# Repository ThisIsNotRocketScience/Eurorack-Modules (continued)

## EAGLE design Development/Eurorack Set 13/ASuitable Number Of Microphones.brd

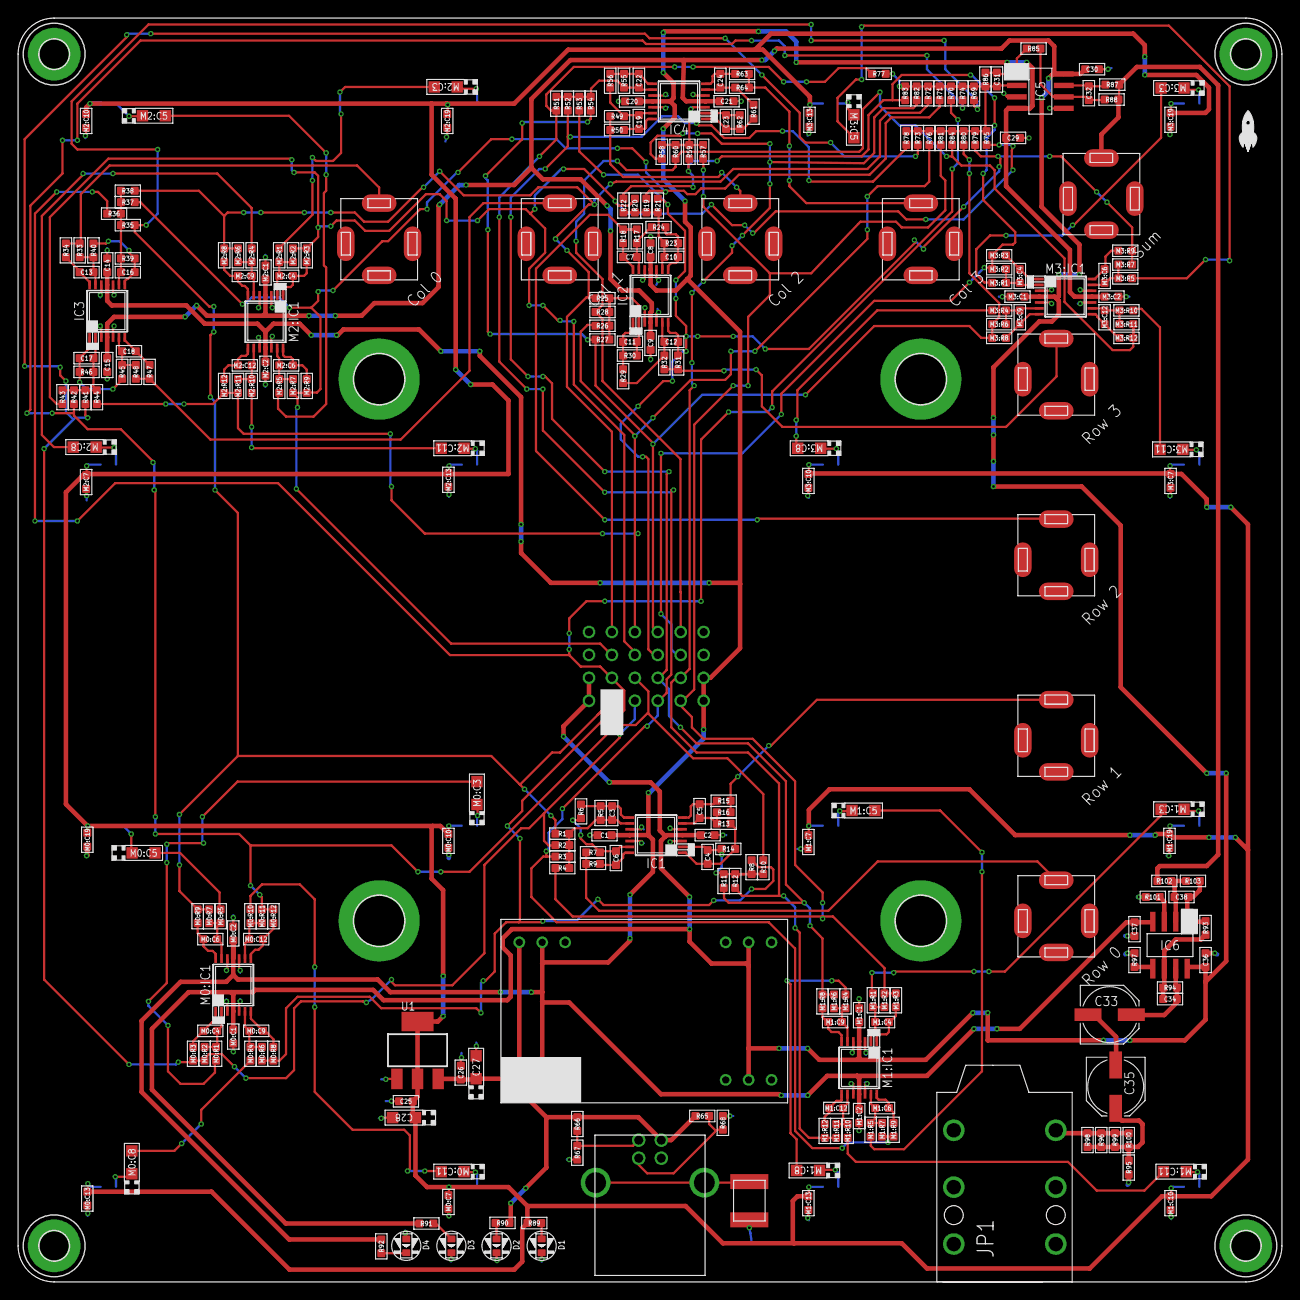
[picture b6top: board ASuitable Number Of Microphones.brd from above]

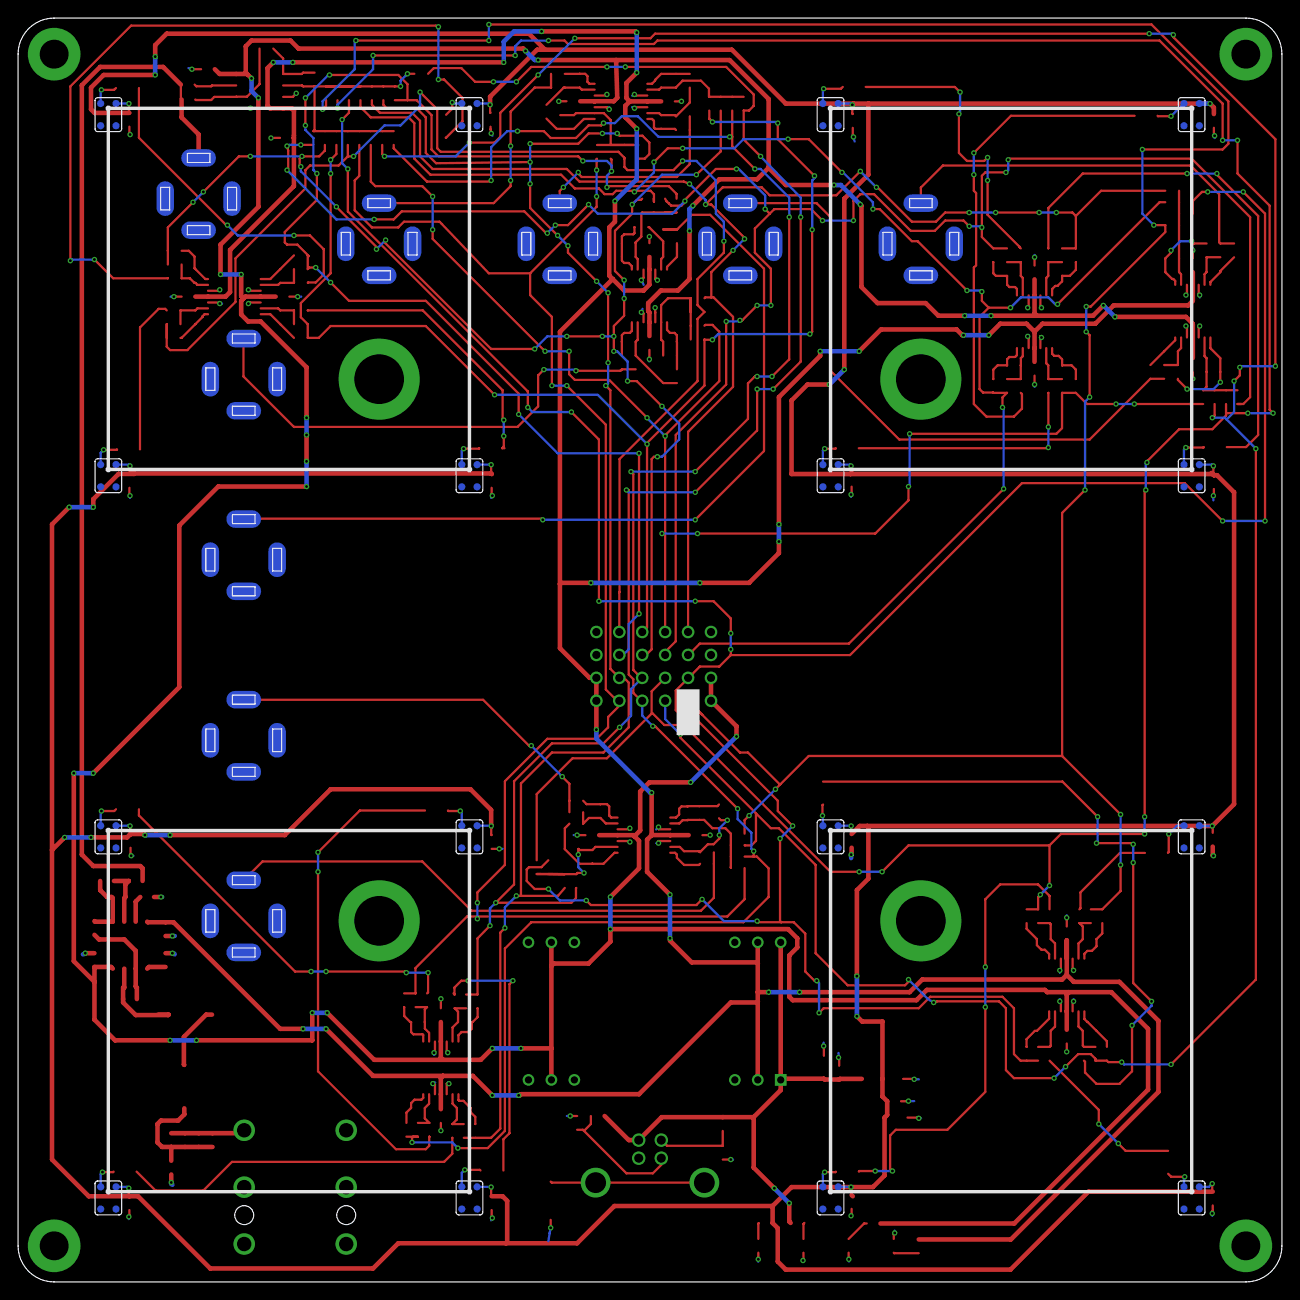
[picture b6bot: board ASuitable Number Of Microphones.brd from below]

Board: 2 copper layers, 140.0 x 140.0 mm, 299 parts (16 on the bottom side), 146 nets.

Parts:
C1, C2, C8, C9, C14, C15, C20, C21, C25, C26, C29, C30, C36, C37: 100n; C0603
C3, C4, C5, C6, C7, C10, C11, C12, C13, C16, C17, C18, C19, C22, C23, C24, C31, C32: 3.3n; C0603
C27, C28: 10u; CASE-A_3216
C33, C35: 100u; PANASONIC_D
C34, C38: 22p; C0603
D1, D2, D3, D4: LED0603
H1, H2, H3, H4: MOUNT-PAD-ROUND5.5; 5,5-PAD
H5, H6, H7, H8: MOUNT-PAD-ROUND3.2; 3,2-PAD
IC1, IC2, IC3, IC4: TL074TSSOP14; TSSOP14
IC5: TL072; SO08
IC6: NE5532D; SO08
J1, J2, J3, J4, J5, J6, J7, J8, J19: JACK; 3.5MM-JACK-SWITCH-13MM-NOHOLES
JP1: AUDIO-JACK-.25-INCH-HORIZ-PTH
L1: FERRITE_1812
M0:C1, M0:C2, M0:C7, M0:C10, M0:C13, M0:C19, M1:C1, M1:C2, M1:C7, M1:C10, M1:C13, M1:C19, M2:C1, M2:C2, M2:C7, M2:C10, M2:C13, M2:C19, M3:C1, M3:C2, M3:C7, M3:C10, M3:C13, M3:C19: 100n; C0603
M0:C3, M0:C5, M0:C8, M0:C11, M1:C3, M1:C5, M1:C8, M1:C11, M2:C3, M2:C5, M2:C8, M2:C11, M3:C3, M3:C5, M3:C8, M3:C11: 1u; CASE-A_3216
M0:C4, M0:C6, M0:C9, M0:C12, M1:C4, M1:C6, M1:C9, M1:C12, M2:C4, M2:C6, M2:C9, M2:C12, M3:C4, M3:C6, M3:C9, M3:C12: 3.3n; C0603
M0:IC1, M1:IC1, M2:IC1, M3:IC1: TL074TSSOP14; TSSOP14
M0:MIC0, M0:MIC1, M0:MIC2, M0:MIC3, M1:MIC0, M1:MIC1, M1:MIC2, M1:MIC3, M2:MIC0, M2:MIC1, M2:MIC2, M2:MIC3, M3:MIC0, M3:MIC1, M3:MIC2, M3:MIC3: SPU0410HR5H-PB
M0:R1, M0:R3, M0:R4, M0:R5, M0:R8, M0:R9, M0:R10, M0:R12, M1:R1, M1:R3, M1:R4, M1:R5, M1:R8, M1:R9, M1:R10, M1:R12, M2:R1, M2:R3, M2:R4, M2:R5, M2:R8, M2:R9, M2:R10, M2:R12, M3:R1, M3:R3, M3:R4, M3:R5, M3:R8, M3:R9, M3:R10, M3:R12: 100; R0603
M0:R2, M0:R6, M0:R7, M0:R11, M1:R2, M1:R6, M1:R7, M1:R11, M2:R2, M2:R6, M2:R7, M2:R11, M3:R2, M3:R6, M3:R7, M3:R11: 100k; R0603
R1, R2, R3, R4, R5, R6, R7, R8, R10, R11, R12, R13, R14, R16, R17, R19, R20, R21, R22, R23, R24, R25, R26, R27, R28, R29, R30, R32, R33, R35, R36, R37, R38, R39, R40, R41, R42, R43, R44, R45, R46, R48, R49, R51, R52, R53, R54, R55, R56, R57, R58, R59, R60, R61, R62, R64, R69, R70, R71, R72, R73, R74, R75, R76, R77, R78, R79, R80, R81, R82, R83, R84, R85, R86, R88: 100k; R0603
R9, R15, R18, R31, R34, R47, R50, R63, R87: 100; R0603
R65, R66: 75k; R0603
R67, R68: 49.9k; R0603
R89: 68; R0603
R90: 150; R0603
R91, R92: 560; R0603
R93, R94, R102, R103: 4.7k; R0603
R95: 56k; R0603
R96, R98, R99, R100: 220; R0603
R97, R101: 27; R0603
U1: CJ1117-3.3-1310190P1; SOT223
U$29: TOOMANYMICROPHONES
U$42: CINCONBRICK_12V; CINCONBRICK
U$51: TINRS_ARTWORKTINYDATE; JUSTATINYROCKET_DATECODE
X1: USB-B-FEMALE; FCI61729

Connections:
3.3V: C25.1, C28.+, M0:C7.2, M0:C10.2, M0:C13.2, M0:C19.2, M0:MIC0.P$1, M0:MIC1.P$1, M0:MIC2.P$1, M0:MIC3.P$1, M1:C7.2, M1:C10.2, M1:C13.2, M1:C19.2, M1:MIC0.P$1, M1:MIC1.P$1, M1:MIC2.P$1, M1:MIC3.P$1, M2:C7.2, M2:C10.2, M2:C13.2, M2:C19.2, M2:MIC0.P$1, M2:MIC1.P$1, M2:MIC2.P$1, M2:MIC3.P$1, M3:C7.2, M3:C10.2, M3:C13.2, M3:C19.2, M3:MIC0.P$1, M3:MIC1.P$1, M3:MIC2.P$1, M3:MIC3.P$1, R89.2, U1.2, U1.TER
5V: C26.1, C27.+, R65.2, R66.2, R90.2, U1.3, U$42.1, U$42.24, X1.1
12V: C2.1, C9.1, C15.1, C21.1, C30.1, C36.2, IC1.4, IC2.4, IC3.4, IC4.4, IC5.8, IC6.8, M0:C1.2, M0:IC1.4, M1:C1.2, M1:IC1.4, M2:C1.2, M2:IC1.4, M3:C1.2, M3:IC1.4, R91.2, U$29.+12@1, U$29.+12@2, U$42.11, U$42.14
-12V: C1.2, C8.2, C14.2, C20.2, C29.2, C37.1, IC1.11, IC2.11, IC3.11, IC4.11, IC5.4, IC6.4, M0:C2.1, M0:IC1.11, M1:C2.1, M1:IC1.11, M2:C2.1, M2:IC1.11, M3:C2.1, M3:IC1.11, R92.1, U$29.-12@1, U$29.-12@2, U$42.2, U$42.23
COL0_SUM: J4.TIP_B@1, J4.TIP_T@3, R33.2, R34.2
COL1_SUM: J5.TIP_B@1, J5.TIP_T@3, R47.2, R48.2
COL2_SUM: J6.TIP_B@1, J6.TIP_T@3, R49.2, R50.2
COL3_SUM: J7.TIP_B@1, J7.TIP_T@3, R63.2, R64.2
GND: C1.1, C2.2, C8.1, C9.2, C14.1, C15.2, C20.1, C21.2, C25.2, C26.2, C27.-, C28.-, C29.1, C30.2, C36.1, C37.2, D1.-, D2.-, D3.-, D4.+, H1.B5,5, H2.B5,5, H3.B5,5, H4.B5,5, IC1.3, IC1.5, IC1.10, IC1.12, IC2.3, IC2.5, IC2.10, IC2.12, IC3.3, IC3.5, IC3.10, IC3.12, IC4.3, IC4.5, IC4.10, IC4.12, IC5.3, IC5.5, J1.RING_B@1, J1.RING_T@3, J2.RING_B@1, J2.RING_T@3, J3.RING_B@1, J3.RING_T@3, J4.RING_B@1, J4.RING_T@3, J5.RING_B@1, J5.RING_T@3, J6.RING_B@1, J6.RING_T@3, J7.RING_B@1, J7.RING_T@3, J8.RING_B@1, J8.RING_T@3, J19.RING_B@1, J19.RING_T@3, JP1.P$2, JP1.P$3, JP1.P$4, L1.P$1, M0:C1.1, M0:C2.2, M0:C7.1, M0:C10.1, M0:C13.1, M0:C19.1, M0:IC1.3, M0:IC1.5, M0:IC1.10, M0:IC1.12, M0:MIC0.P$2, M0:MIC0.P$3, M0:MIC1.P$2, M0:MIC1.P$3, M0:MIC2.P$2, M0:MIC2.P$3, M0:MIC3.P$2, M0:MIC3.P$3, M1:C1.1, M1:C2.2, M1:C7.1, M1:C10.1, M1:C13.1, M1:C19.1, M1:IC1.3, M1:IC1.5, M1:IC1.10, M1:IC1.12, M1:MIC0.P$2, M1:MIC0.P$3, M1:MIC1.P$2, M1:MIC1.P$3, M1:MIC2.P$2, M1:MIC2.P$3, M1:MIC3.P$2, M1:MIC3.P$3, M2:C1.1, M2:C2.2, M2:C7.1, M2:C10.1, M2:C13.1, M2:C19.1, M2:IC1.3, M2:IC1.5, M2:IC1.10, M2:IC1.12, M2:MIC0.P$2, M2:MIC0.P$3, M2:MIC1.P$2, M2:MIC1.P$3, M2:MIC2.P$2, M2:MIC2.P$3, M2:MIC3.P$2, M2:MIC3.P$3, M3:C1.1, M3:C2.2, M3:C7.1, M3:C10.1, M3:C13.1, M3:C19.1, M3:IC1.3, M3:IC1.5, M3:IC1.10, M3:IC1.12, M3:MIC0.P$2, M3:MIC0.P$3, M3:MIC1.P$2, M3:MIC1.P$3, M3:MIC2.P$2, M3:MIC2.P$3, M3:MIC3.P$2, M3:MIC3.P$3, R67.1, R68.1, R95.2, R97.2, R101.2, U1.1, U$29.GND@1, U$29.GND@2, U$29.GND@3, U$29.GND@4, U$42.3, U$42.10, U$42.12, U$42.13, U$42.15, U$42.22, X1.4
M0:N$1: M0:C6.2, M0:IC1.13, M0:R5.2, M0:R7.1
M0:N$2: M0:C6.1, M0:IC1.14, M0:R9.1
M0:N$3: M0:C4.2, M0:IC1.2, M0:R1.2, M0:R2.1
M0:N$4: M0:C4.1, M0:IC1.1, M0:R3.1
M0:N$5: M0:C9.2, M0:IC1.6, M0:R4.2, M0:R6.1
M0:N$7: M0:C12.2, M0:IC1.9, M0:R10.2, M0:R11.1
M0:N$9: M0:C9.1, M0:IC1.7, M0:R8.1
M0:N$10: M0:C12.1, M0:IC1.8, M0:R12.1
M0:N$14: M0:C11.-, M0:R10.1
M0:N$15: M0:C11.+, M0:MIC3.P$4
M0:N$16: M0:C8.+, M0:MIC2.P$4
M0:N$17: M0:C5.-, M0:R5.1
M0:N$18: M0:C5.+, M0:MIC0.P$4
M0:N$19: M0:C8.-, M0:R4.1
M0:N$20: M0:C3.+, M0:MIC1.P$4
M0:N$21: M0:C3.-, M0:R1.1
M1:N$1: M1:C6.2, M1:IC1.13, M1:R5.2, M1:R7.1
M1:N$2: M1:C6.1, M1:IC1.14, M1:R9.1
M1:N$3: M1:C4.2, M1:IC1.2, M1:R1.2, M1:R2.1
M1:N$4: M1:C4.1, M1:IC1.1, M1:R3.1
M1:N$5: M1:C9.2, M1:IC1.6, M1:R4.2, M1:R6.1
M1:N$7: M1:C12.2, M1:IC1.9, M1:R10.2, M1:R11.1
M1:N$9: M1:C9.1, M1:IC1.7, M1:R8.1
M1:N$10: M1:C12.1, M1:IC1.8, M1:R12.1
M1:N$14: M1:C11.-, M1:R10.1
M1:N$15: M1:C11.+, M1:MIC3.P$4
M1:N$16: M1:C8.+, M1:MIC2.P$4
M1:N$17: M1:C5.-, M1:R5.1
M1:N$18: M1:C5.+, M1:MIC0.P$4
M1:N$19: M1:C8.-, M1:R4.1
M1:N$20: M1:C3.+, M1:MIC1.P$4
M1:N$21: M1:C3.-, M1:R1.1
M2:N$1: M2:C6.2, M2:IC1.13, M2:R5.2, M2:R7.1
M2:N$2: M2:C6.1, M2:IC1.14, M2:R9.1
M2:N$3: M2:C4.2, M2:IC1.2, M2:R1.2, M2:R2.1
M2:N$4: M2:C4.1, M2:IC1.1, M2:R3.1
M2:N$5: M2:C9.2, M2:IC1.6, M2:R4.2, M2:R6.1
M2:N$7: M2:C12.2, M2:IC1.9, M2:R10.2, M2:R11.1
M2:N$9: M2:C9.1, M2:IC1.7, M2:R8.1
M2:N$10: M2:C12.1, M2:IC1.8, M2:R12.1
M2:N$14: M2:C11.-, M2:R10.1
M2:N$15: M2:C11.+, M2:MIC3.P$4
M2:N$16: M2:C8.+, M2:MIC2.P$4
M2:N$17: M2:C5.-, M2:R5.1
M2:N$18: M2:C5.+, M2:MIC0.P$4
M2:N$19: M2:C8.-, M2:R4.1
M2:N$20: M2:C3.+, M2:MIC1.P$4
M2:N$21: M2:C3.-, M2:R1.1
M3:N$1: M3:C6.2, M3:IC1.13, M3:R5.2, M3:R7.1
M3:N$2: M3:C6.1, M3:IC1.14, M3:R9.1
M3:N$3: M3:C4.2, M3:IC1.2, M3:R1.2, M3:R2.1
M3:N$4: M3:C4.1, M3:IC1.1, M3:R3.1
M3:N$5: M3:C9.2, M3:IC1.6, M3:R4.2, M3:R6.1
M3:N$7: M3:C12.2, M3:IC1.9, M3:R10.2, M3:R11.1
M3:N$9: M3:C9.1, M3:IC1.7, M3:R8.1
M3:N$10: M3:C12.1, M3:IC1.8, M3:R12.1
M3:N$14: M3:C11.-, M3:R10.1
M3:N$15: M3:C11.+, M3:MIC3.P$4
M3:N$16: M3:C8.+, M3:MIC2.P$4
M3:N$17: M3:C5.-, M3:R5.1
M3:N$18: M3:C5.+, M3:MIC0.P$4
M3:N$19: M3:C8.-, M3:R4.1
M3:N$20: M3:C3.+, M3:MIC1.P$4
M3:N$21: M3:C3.-, M3:R1.1
unnamed: C3.1, IC1.9, R1.2, R2.2, R3.2, R4.2, R5.1
unnamed: C6.1, IC1.14, R9.1
unnamed: C6.2, IC1.13, R6.2, R7.1
unnamed: L1.P$2, X1.P$1, X1.P$2
unnamed: R66.1, R67.2, X1.2
unnamed: R65.1, R68.2, X1.3
unnamed: C31.1, IC5.2, R69.2, R70.2, R71.2, R72.2, R73.2, R74.2, R75.2, R76.2, R77.2, R78.2, R79.2, R80.2, R81.2, R82.2, R83.2, R84.2, R86.1
unnamed: C3.2, IC1.8, R5.2, R6.1
unnamed: C4.1, IC1.2, R8.2, R10.2, R11.2, R12.2, R14.1
unnamed: C33.-, C35.-
unnamed: D1.+, R89.1
unnamed: D2.+, R90.1
unnamed: D3.+, R91.1
unnamed: C4.2, IC1.1, R13.1, R14.2
unnamed: C5.1, IC1.7, R15.1
unnamed: C5.2, IC1.6, R13.2, R16.1
unnamed: C10.1, IC2.9, R19.2, R20.2, R21.2, R22.2, R23.1
unnamed: C7.1, IC2.14, R18.1
unnamed: D4.-, R92.2
unnamed: C31.2, IC5.1, R85.1, R86.2
unnamed: C32.1, IC5.7, R87.1
unnamed: C32.2, IC5.6, R85.2, R88.1
unnamed: C7.2, IC2.13, R17.1, R24.2
unnamed: C10.2, IC2.8, R23.2, R24.1
unnamed: C11.1, IC2.2, R25.2, R26.2, R27.2, R28.2, R30.1
unnamed: C34.1, IC6.6, R93.1, R94.2
unnamed: C33.+, C34.2, IC6.7, R94.1
unnamed: C35.+, R95.1, R96.1, R98.1, R99.1, R100.1
unnamed: IC6.5, R97.1
unnamed: C11.2, IC2.1, R29.1, R30.2
unnamed: C12.1, IC2.7, R31.1
unnamed: C12.2, IC2.6, R29.2, R32.1
unnamed: C16.1, IC3.9, R35.2, R36.2, R37.2, R38.2, R39.1
unnamed: C13.1, IC3.14, R34.1
unnamed: IC6.3, R101.1
unnamed: C38.1, IC6.2, R102.1, R103.2
unnamed: C38.2, IC6.1, R93.2, R103.1
unnamed: C13.2, IC3.13, R33.1, R40.2
unnamed: C16.2, IC3.8, R39.2, R40.1
unnamed: C17.1, IC3.2, R41.2, R42.2, R43.2, R44.2, R46.1
unnamed: C17.2, IC3.1, R45.1, R46.2
unnamed: C18.1, IC3.7, R47.1
unnamed: C18.2, IC3.6, R45.2, R48.1
unnamed: C22.1, IC4.9, R51.2, R52.2, R53.2, R54.2, R55.1
unnamed: C19.1, IC4.14, R50.1
unnamed: C19.2, IC4.13, R49.1, R56.2
unnamed: C22.2, IC4.8, R55.2, R56.1
unnamed: C23.1, IC4.2, R57.2, R58.2, R59.2, R60.2, R62.1
unnamed: C23.2, IC4.1, R61.1, R62.2
unnamed: C24.1, IC4.7, R63.1
unnamed: C24.2, IC4.6, R61.2, R64.1
OUTTIPLEFT: JP1.P$6, R96.2, R98.2, R99.2, R100.2
R0M0: M0:R7.2, M0:R9.2, R1.1, R35.1, R69.1, U$29.P$1
R0M1: M0:R2.2, M0:R3.2, R2.1, R41.1, R73.1, U$29.P$2
R0M2: M1:R7.2, M1:R9.2, R3.1, R51.1, R77.1, U$29.P$3
R0M3: M1:R2.2, M1:R3.2, R4.1, R57.1, R81.1, U$29.P$4
R1M0: M0:R6.2, M0:R8.2, R8.1, R36.1, R70.1, U$29.P$5
R1M1: M0:R11.2, M0:R12.2, R10.1, R42.1, R74.1, U$29.P$6
R1M2: M1:R6.2, M1:R8.2, R11.1, R52.1, R78.1, U$29.P$7
R1M3: M1:R11.2, M1:R12.2, R12.1, R58.1, R82.1, U$29.P$8
R2M0: M2:R7.2, M2:R9.2, R19.1, R37.1, R71.1, U$29.P$9
R2M1: M2:R2.2, M2:R3.2, R20.1, R43.1, R75.1, U$29.P$10
R2M2: M3:R7.2, M3:R9.2, R21.1, R53.1, R79.1, U$29.P$11
R2M3: M3:R2.2, M3:R3.2, R22.1, R59.1, R83.1, U$29.P$12
R3M0: M2:R6.2, M2:R8.2, R25.1, R38.1, R72.1, U$29.P$13
R3M1: M2:R11.2, M2:R12.2, R26.1, R44.1, R76.1, U$29.P$14
R3M2: M3:R6.2, M3:R8.2, R27.1, R54.1, R80.1, U$29.P$15
R3M3: M3:R11.2, M3:R12.2, R28.1, R60.1, R84.1, U$29.P$16
ROW0_SUM: J19.TIP_B@1, J19.TIP_T@3, R7.2, R9.2
ROW1_SUM: J1.TIP_B@1, J1.TIP_T@3, R15.2, R16.2
ROW2_SUM: J2.TIP_B@1, J2.TIP_T@3, R17.2, R18.2
ROW3_SUM: J3.TIP_B@1, J3.TIP_T@3, R31.2, R32.2
TOTALSUM: J8.TIP_B@1, J8.TIP_T@3, R87.2, R88.2, R102.2

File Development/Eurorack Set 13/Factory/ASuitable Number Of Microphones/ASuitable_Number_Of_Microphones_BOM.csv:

Comment,Designator,Footprint,LCSC Part #,combinedname,name
100n,"M0:C1, M0:C10, M0:C13, M0:C19, M0:C2, M0:C7, C1, C2, M1:C1, M1:C10, M1:C13, M1:C19, M1:C2, M1:C7, C8, C9, M2:C1, M2:C10, M2:C13, M2:C19, M2:C2, M2:C7, M3:C1, M3:C10, M3:C13, M3:C19, M3:C2, M3:C7, C14, C15, C20, C21, C25, C26, C29, C30, C36, C37",C0603,,C*_C0603_100n,C*
3.3n,"M0:C12, M0:C4, M0:C6, M0:C9, C6, C3, M1:C12, M1:C4, M1:C6, M1:C9, C4, C5, C7, C10, C11, C12, M2:C12, M2:C4, M2:C6, M2:C9, M3:C12, M3:C4, M3:C6, M3:C9, C13, C16, C17, C18, C19, C22, C23, C24, C31, C32",C0603,,C*_C0603_3.3n,C*
22p,"C34, C38",C0603,,C*_C0603_22p,C*
1u,"M0:C11, M0:C3, M0:C5, M0:C8, M1:C11, M1:C3, M1:C5, M1:C8, M2:C11, M2:C3, M2:C5, M2:C8, M3:C11, M3:C3, M3:C5, M3:C8",CASE-A_3216,,C-POLAR*_CASE-A_3216_1u,C-POLAR*
10u,"C27, C28",CASE-A_3216,,C-POLAR*_CASE-A_3216_10u,C-POLAR*
TL074TSSOP14,"M0:IC1, IC1, M1:IC1, IC2, M2:IC1, M3:IC1, IC3, IC4",TSSOP14,,TL074_TSSOP14_TL074TSSOP14,TL074
100,"M0:R1, M0:R10, M0:R12, M0:R3, M0:R4, M0:R5, M0:R8, M0:R9, R9, M1:R1, M1:R10, M1:R12, M1:R3, M1:R4, M1:R5, M1:R8, M1:R9, R15, R18, R31, M2:R1, M2:R10, M2:R12, M2:R3, M2:R4, M2:R5, M2:R8, M2:R9, M3:R1, M3:R10, M3:R12, M3:R3, M3:R4, M3:R5, M3:R8, M3:R9, R34, R47, R50, R63, R87",R0603,,R*_R0603_100,R*
100k,"M0:R11, M0:R2, M0:R6, M0:R7, R7, R1, R2, R3, R4, R5, R6, R8, R10, R11, R12, M1:R11, M1:R2, M1:R6, M1:R7, R13, R14, R16, R17, R19, R20, R21, R22, R23, R24, R25, R26, R27, R28, R29, R30, R32, M2:R11, M2:R2, M2:R6, M2:R7, M3:R11, M3:R2, M3:R6, M3:R7, R33, R35, R36, R37, R38, R39, R40, R41, R42, R43, R44, R45, R46, R48, R49, R51, R52, R53, R54, R55, R56, R57, R58, R59, R60, R61, R62, R64, R69, R70, R71, R72, R73, R74, R75, R76, R77, R78, R79, R80, R81, R82, R83, R84, R85, R86, R88",R0603,,R*_R0603_100k,R*
75k,"R65, R66",R0603,,R*_R0603_75k,R*
49.9k,"R67, R68",R0603,,R*_R0603_49.9k,R*
68,"R89",R0603,,R*_R0603_68,R*
150,"R90",R0603,,R*_R0603_150,R*
560,"R91, R92",R0603,,R*_R0603_560,R*
4.7k,"R93, R94, R102, R103",R0603,,R*_R0603_4.7k,R*
56k,"R95",R0603,,R*_R0603_56k,R*
220,"R96, R98, R99, R100",R0603,,R*_R0603_220,R*
27,"R97, R101",R0603,,R*_R0603_27,R*
SPU0410HR5H-PB,"M0:MIC1, M0:MIC0, M0:MIC2, M0:MIC3, M1:MIC0, M1:MIC1, M1:MIC2, M1:MIC3, M2:MIC0, M2:MIC1, M2:MIC2, M2:MIC3, M3:MIC0, M3:MIC1, M3:MIC2, M3:MIC3",SPU0410HR5H-PB,,SPU0410HR5H-PB_SPU0410HR5H-PB_SPU0410HR5H-PB,SPU0410HR5H-PB
JACK,"J19, J1, J2, J3, J4, J5, J6, J7, J8",3.5MM-JACK-SWITCH-13MM-NOHOLES,,AUDIO-JACK_SMALLSYMBOL_3.5MM-JACK-SWITCH-13MM-NOHOLES_JACK,AUDIO-JACK_SMALLSYMBOL
TOOMANYMICROPHONES,"U$29",TOOMANYMICROPHONES,,TOOMANYMICROPHONES_TOOMANYMICROPHONES_TOOMANYMICROPHONES,TOOMANYMICROPHONES
MOUNT-PAD-ROUND5.5,"H1, H2, H3, H4",5,5-PAD,,MOUNT-PAD-ROUND_5.5-PAD_MOUNT-PAD-ROUND5.5,MOUNT-PAD-ROUND
MOUNT-PAD-ROUND3.2,"H5, H6, H7, H8",3,2-PAD,,MOUNT-PAD-ROUND_3.2-PAD_MOUNT-PAD-ROUND3.2,MOUNT-PAD-ROUND
USB-B-FEMALE,"X1",FCI61729,,USB-B-FEMALE_FCI61729_USB-B-FEMALE,USB-B-FEMALE
FERRITE_1812,"L1",FERRITE_1812,,FERRITE_FERRITE_1812_FERRITE_1812,FERRITE
CJ1117-3.3-1310190P1,"U1",SOT223,,CJ1117-3.3_SOT223_CJ1117-3.3-1310190P1,CJ1117-3.3
TL072,"IC5",SO08,,TL072_SO08_TL072,TL072
CINCONBRICK_12V,"U$42",CINCONBRICK,,CINCONBRICK_12V_CINCONBRICK_CINCONBRICK_12V,CINCONBRICK_12V
,"D1, D2, D3, D4",LED0603,,LED*_LED0603_,LED*
NE5532D,"IC6",SO08,,NE5532_SO08_NE5532D,NE5532
100u,"C33, C35",PANASONIC_D,,CPOL-US_PANASONIC_D_100u,CPOL-US
,"JP1",AUDIO-JACK-.25-INCH-HORIZ-PTH,,AUDIO-JACK4-.25-HORIZ-TRS_AUDIO-JACK-.25-INCH-HORIZ-PTH_,AUDIO-JACK4-.25-HORIZ-TRS
TINRS_ARTWORKTINYDATE,"U$51",JUSTATINYROCKET_DATECODE,,TINRS_ARTWORK_JUSTATINYROCKET_DATECODE_TINRS_ARTWORKTINYDATE,TINRS_ARTWORK

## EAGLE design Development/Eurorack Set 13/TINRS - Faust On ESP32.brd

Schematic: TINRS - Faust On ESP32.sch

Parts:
C1, C2, C3, C32, C35, C36, C37, C39: 3.3nF; C0603
C4, C6, C13, C19, C23, C24, C25, C28, C29: 10u; CASE-A_3216
C5, C38: 100nF; C0603; MPN MC0603F104Z160CT
C7, C8, C14, C15, C16, C20, C21, C22, C26, C27, C40, C41: 100n; C0603
C9, C10: CPOL-US153CLV-0605; 153CLV-0605
C11, C42: 33n; C0603
C17, C18: 22p; C0603
C30, C31: 18p; C0603
C33: 10uF; CASE-A_3216; MPN TAJB106K020RNJ
C34: 100nF; C0603; MPN 06035C104KAT2A
CN1: USBMINIB; USB-MINIB
D1, D2: D-SMA; DO-214AC
D3, D4, D5, D6: BAS16W; SOT-323
D7, D8: yellow; LED0603
IC1, IC4: MCP6004; SO14; MPN MCP6004-I/SL.
IC2: TL072; SO08
J1, J2, J3, J4, J8, J9, J10, J11, J12, J13, J14: JACK; 3.5MM-JACK-SWITCH-13MM-NOHOLES
J15: POWERSHROUDED; POWER_16_SHROUDED
JP1, JP2: M02PTH; 1X02
JP3: JUMPER-2PTH; 1X02
JP4: M03X2; 2X3-SHROUDED
L1, L2: L-0805; L0805
PCB1: EURORACK_PCB12HP; EURORACK12HPPCB
Q1, Q2: MMBT3904; SOT23-BEC; MPN PMBT3904,215
R1, R2, R3, R4, R5, R6, R7: POTSQUAREHOLE_SMALLKNOB; ALPS_POT_SQUAREHOLES
R8, R9: 1.5k; R0603
R10, R11, R50, R53: 56; R0603
R12, R13, R15, R26, R31, R73: 10k; R0603
R14, R19, R22, R23, R25, R27, R30, R33, R36, R38, R39, R42, R43, R45, R47, R49, R52, R55: 33k; R0603
R16, R18, R21, R24, R29, R32, R35, R40, R46, R51, R54, R72: 100k; R0603
R17, R20, R28, R34, R37, R41, R44, R48: 51k; R0603
SJ1, SJ2: SOLDERJUMPERNC; SJ_2S
U1: ESP-WROOM-32
U2, U3: LD1117S; SOT-223
U4: LM4040DIM3-5.0; SOT95P237X112-3N
U$1, U$2: SWITCH_W_LED_PB6149L-X-102YELLOW; PB6149L
U$9: WM8731; 28-SSOP
U$12: CH340G; SO16
U$13: 12MHZ; 16MHZXTAL
X1: 12.288MHZ; 2P-SMD-5.0X3.2

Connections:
3.3V: C5.1, C21.2, C24.+ (1), C25.+ (1), C26.1, C38.1, IC1.4 (V+), IC4.4 (V+), JP4.5, R1.P$3 (A), R2.P$3 (A), R3.P$3 (A), R4.P$3 (A), R5.P$3 (A), R6.P$3 (A), R7.P$3 (A), R8.2, R9.1, R12.2, R13.2, R15.2, R31.2, R73.2, U1.2 (3V3), U2.2 (OUT), U2.TER (OUT), U$9.P$1 (DBVDD), U$9.P$21 (MODE), U$9.P$27 (DCVDD)
3V3_A: C15.2, C29.+ (1), U3.2 (OUT), U3.TER (OUT), U$9.P$8 (HPVDD), U$9.P$14 (AVDD)
12V: C4.+ (1), C8.1, C16.2, C22.2, C23.+ (1), C28.+ (1), C41.1, D1.2 (-), IC2.8 (V+), U2.3 (IN), U3.3 (IN)
-12V: C6.- (2), C7.2, C33.- (2), C40.2, D2.1 (+), IC2.4 (V-), R26.1
ANALOG0: C3.2, IC4.14 (OUT), R22.1, U1.4 (SENSOR_VP)
ANALOG1: C1.2, IC4.8 (OUT), R14.1, U1.5 (SENSOR_VN)
ANALOG2: C2.2, IC4.1 (OUT), R19.1, U1.6 (IO34)
ANALOG3: C32.2, IC4.7 (OUT), R25.1, U1.7 (IO35)
ANALOG4: C37.2, IC1.14 (OUT), R42.1, U1.8 (IO32)
ANALOG5: C35.2, IC1.8 (OUT), R33.1, U1.23 (IO15)
ANALOG6: C36.2, IC1.1 (OUT), R36.1, U1.24 (IO2)
ANALOG7: C39.2, IC1.7 (OUT), R47.1, U1.26 (IO4)
CODEC_VMID: C13.+ (1), C14.1, U$9.P$16 (VMID)
DEFAULTGATE1: D3.CATHODE
DEFAULTGATE2: D4.CATHODE
ESP->USB: D8.-, JP4.4, U1.35 (TXD0), U$12.3 (RXD)
ESP_BOOT: JP3.1, JP4.1, SJ2.2, U1.25 (IO0)
ESP_EN: C27.1, JP4.6, R15.1, SJ1.2, U1.3 (EN)
GATEJACK: Q1.C, R31.1, U1.32 (NC)
GND: C4.- (2), C5.2, C6.+ (1), C7.1, C8.2, C13.- (2), C14.2, C15.1, C16.1, C17.2, C18.1, C19.- (2), C20.2, C21.1, C22.1, C23.- (2), C24.- (2), C25.- (2), C26.2, C27.2, C28.- (2), C29.- (2), C30.1, C31.1, C33.+ (1), C34.1, C38.2, C40.1, C41.2, CN1.GND, IC1.3 (+IN), IC1.5 (+IN), IC1.10 (+IN), IC1.11 (V-), IC1.12 (+IN), IC2.3 (+IN), IC2.5 (+IN), IC4.3 (+IN), IC4.5 (+IN), IC4.10 (+IN), IC4.11 (V-), IC4.12 (+IN), J1.RING_B@1 (RING), J1.RING_T@3 (RING), J1.SWITCH_B@1 (SWITCH), J1.SWITCH_T@3 (SWITCH), J2.RING_B@1 (RING), J2.RING_T@3 (RING), J2.SWITCH_B@1 (SWITCH), J2.SWITCH_T@3 (SWITCH), J3.RING_B@1 (RING), J3.RING_T@3 (RING), J3.SWITCH_B@1 (SWITCH), J3.SWITCH_T@3 (SWITCH), J4.RING_B@1 (RING), J4.RING_T@3 (RING), J8.RING_B@1 (RING), J8.RING_T@3 (RING), J9.RING_B@1 (RING), J9.RING_T@3 (RING), J9.SWITCH_B@1 (SWITCH), J9.SWITCH_T@3 (SWITCH), J10.RING_B@1 (RING), J10.RING_T@3 (RING), J10.SWITCH_B@1 (SWITCH), J10.SWITCH_T@3 (SWITCH), J11.RING_B@1 (RING), J11.RING_T@3 (RING), J11.SWITCH_B@1 (SWITCH), J11.SWITCH_T@3 (SWITCH), J12.RING_B@1 (RING), J12.RING_T@3 (RING), J12.SWITCH_B@1 (SWITCH), J12.SWITCH_T@3 (SWITCH), J13.RING_B@1 (RING), J13.RING_T@3 (RING), J13.SWITCH_B@1 (SWITCH), J13.SWITCH_T@3 (SWITCH), J14.RING_B@1 (RING), J14.RING_T@3 (RING), J14.SWITCH_B@1 (SWITCH), J14.SWITCH_T@3 (SWITCH), J15.3 (GND), J15.4 (GND), J15.5 (GND), J15.6 (GND), J15.7 (GND), J15.8 (GND), JP3.2, JP4.3, Q1.E, Q2.E, R1.P$1 (E), R2.P$1 (E), R3.P$1 (E), R4.P$1 (E), R5.P$1 (E), R6.P$1 (E), R7.P$1 (E), U1.1 (GND), U1.15 (GND), U1.38 (GND), U1.GND, U2.1 (GND), U3.1 (GND), U4.1 (CATHODE), U$1.3, U$1.4, U$1.LEDNEG (NEG), U$2.3, U$2.4, U$2.LEDNEG (NEG), U$9.P$11 (HPGND), U$9.P$15 (AGND), U$9.P$28 (DGND), U$12.1 (GND), U$13.P$2 (GND), U$13.P$4 (GND)
I2S_LRCK: U1.11 (IO26), U$9.P$5 (DACLRC), U$9.P$7 (ADCLRC)
I2S_SCK: U1.12 (IO27), U$9.P$3 (BCLK)
I2S_SIN: U1.10 (IO25), U$9.P$6 (ADCDAT)
I2S_SOUT: U1.9 (IO33), U$9.P$4 (DACDAT)
KNOB_DECAY: R2.P$2 (S), R43.2
KNOB_DELAYBEFORETAIL: R5.P$2 (S), R45.2
KNOB_MOD: R39.2
KNOB_PITCH: R1.P$2 (S), R49.2
KNOB_SPACE: R6.P$2 (S), R23.2
KNOB_TONE: R3.P$2 (S), R38.2
KNOB_TRIGGERSPACE: R7.P$2 (S), R30.2
KNOB_TRIGGERTYPE: R4.P$2 (S), R27.2
unnamed: D8.+, R8.1
unnamed: D7.+, R9.2
unnamed: SJ2.1, U$12.13 (DTR)
unnamed: SJ1.1, U$12.14 (RTS)
unnamed: C17.1, U$12.7 (XTAL_IN), U$13.P$1 (XTAL1)
unnamed: C18.2, U$12.8 (XTAL_OUT), U$13.P$3 (XTAL2)
unnamed: CN1.D+, U$12.5 (D+)
unnamed: D5.CATHODE, D6.ANODE
unnamed: CN1.VBUS, D5.ANODE
unnamed: C19.+ (1), C20.1, D6.CATHODE, U$12.4 (3V3), U$12.16 (VCC)
unnamed: CN1.D-, U$12.6 (D-)
unnamed: C30.2, U$9.P$26 (XTO), X1.2
unnamed: J15.9 (+12V), J15.10 (+12V), L1.2
unnamed: J15.1 (-12V), J15.2 (-12V), L2.2
unnamed: D1.1 (+), L1.1
unnamed: D2.2 (-), L2.1
unnamed: J15.15 (GATE), J15.16 (GATE), JP1.1, JP2.1
unnamed: D3.ANODE, JP1.2
unnamed: D4.ANODE, JP2.2
unnamed: R10.2, U$1.LEDPOS (POS)
unnamed: R11.2, U$2.LEDPOS (POS)
unnamed: J10.TIP_B@1 (TIP), J10.TIP_T@3 (TIP), R16.2
unnamed: C1.1, IC4.9 (-IN), R14.2, R16.1, R17.1, R23.1
unnamed: J12.TIP_B@1 (TIP), J12.TIP_T@3 (TIP), R18.2
unnamed: C2.1, IC4.2 (-IN), R18.1, R19.2, R20.1, R27.1
unnamed: C31.2, U$9.P$25 (XTI/MCLK), X1.1
unnamed: J9.TIP_B@1 (TIP), J9.TIP_T@3 (TIP), R24.2
unnamed: C32.1, IC4.6 (-IN), R24.1, R25.2, R41.1, R43.1
unnamed: Q1.B, R29.2
unnamed: J2.TIP_B@1 (TIP), J2.TIP_T@3 (TIP), R29.1
unnamed: J13.TIP_B@1 (TIP), J13.TIP_T@3 (TIP), R21.2
unnamed: C3.1, IC4.13 (-IN), R21.1, R22.2, R28.1, R30.1
unnamed: J11.TIP_B@1 (TIP), J11.TIP_T@3 (TIP), R32.2
unnamed: C35.1, IC1.9 (-IN), R32.1, R33.2, R34.1, R38.1
unnamed: C36.1, IC1.2 (-IN), R35.1, R36.2, R37.1, R39.1
unnamed: J14.TIP_B@1 (TIP), J14.TIP_T@3 (TIP), R40.2
unnamed: C37.1, IC1.13 (-IN), R40.1, R42.2, R44.1, R45.1
unnamed: J1.TIP_B@1 (TIP), J1.TIP_T@3 (TIP), R46.2
unnamed: C39.1, IC1.6 (-IN), R46.1, R47.2, R48.1, R49.1
unnamed: C42.1, IC2.1 (OUT), R50.2
unnamed: Q2.B, R72.2
unnamed: J3.TIP_B@1 (TIP), J3.TIP_T@3 (TIP), R72.1
unnamed: C42.2, IC2.2 (-IN), R51.2, R52.1
unnamed: J4.TIP_B@1 (TIP), J4.TIP_T@3 (TIP), R50.1, R51.1
unnamed: C10.+, U$9.P$12 (LOUT)
unnamed: C9.+, U$9.P$13 (ROUT)
unnamed: C10.-, R52.2
unnamed: C11.1, IC2.7 (OUT), R53.2
unnamed: C11.2, IC2.6 (-IN), R54.2, R55.1
unnamed: J8.TIP_B@1 (TIP), J8.TIP_T@3 (TIP), R53.1, R54.1
unnamed: C9.-, R55.2
REF_-5V: C34.2, R17.2, R20.2, R26.2, R28.2, R34.2, R37.2, R41.2, R44.2, R48.2, U4.2 (ANODE)
SPI_MISO: U1.14 (IO12)
SPI_MOSI: U1.16 (IO13), U$9.P$23 (SDIN)
SPI_SCK: U1.13 (IO14), U$9.P$24 (SCLK)
TRIGGER1: R13.1, U1.30 (IO18), U$1.1, U$1.2
TRIGGER2: R12.1, U1.28 (IO17), U$2.1, U$2.2
TRIGGERJACK: Q2.C, R73.1, U1.31 (IO19)
TRIGGERLED1: R10.1, U1.29 (IO5)
TRIGGERLED2: R11.1, U1.27 (IO16)
USB->ESP: D7.-, JP4.2, U1.34 (RXD0), U$12.2 (TXD)
WM_CS: U1.33 (IO21), U$9.P$22 (CSB)

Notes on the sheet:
-5.0 to 5.0 -> 3.3 -> 0.0

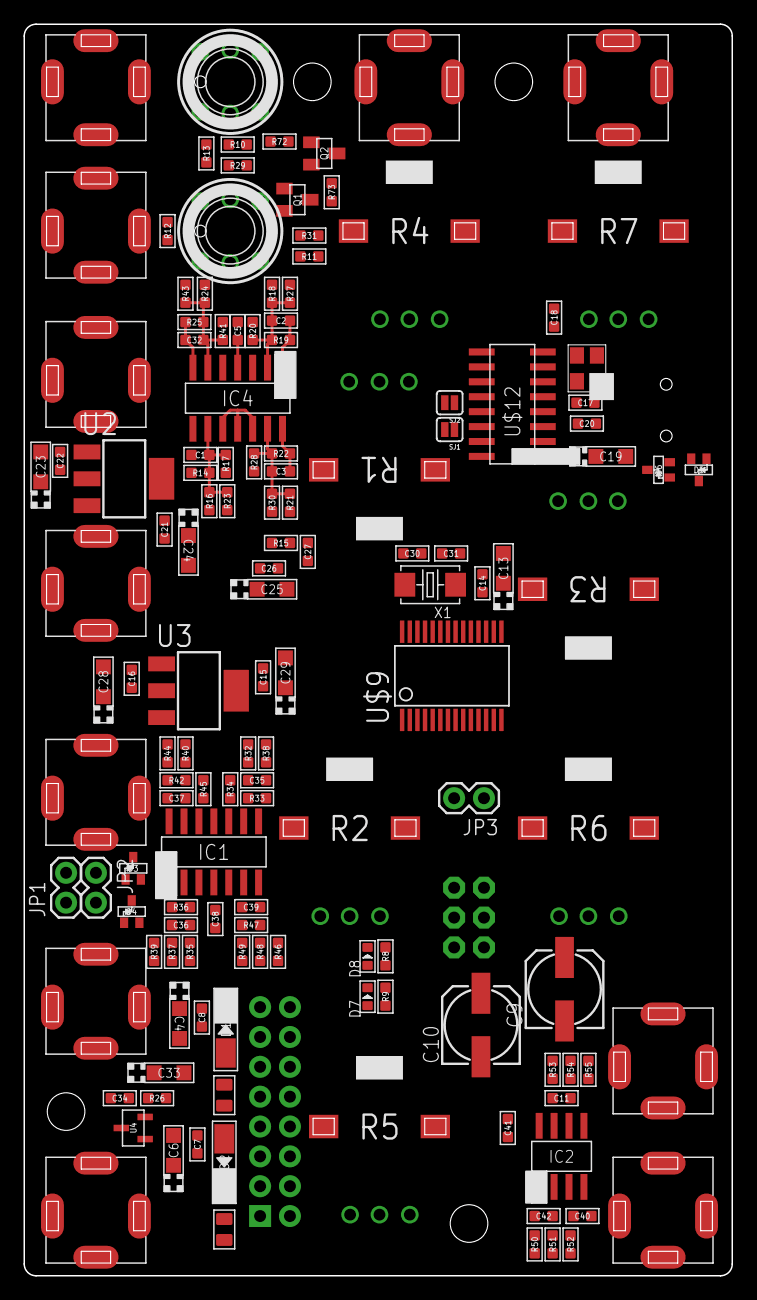
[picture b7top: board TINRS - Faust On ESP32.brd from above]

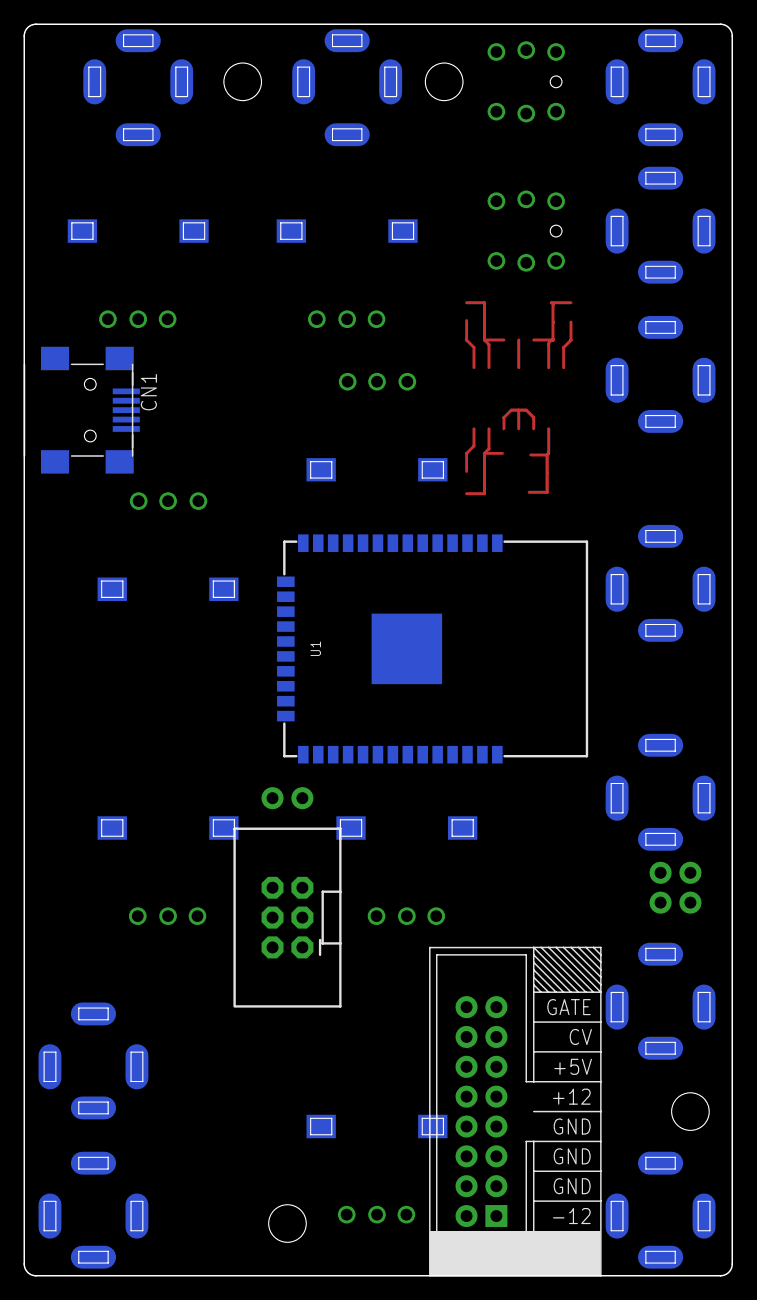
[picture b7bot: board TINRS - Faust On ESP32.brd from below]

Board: 2 copper layers, 60.2 x 106.5 mm, 143 parts (4 on the bottom side), 90 nets.
